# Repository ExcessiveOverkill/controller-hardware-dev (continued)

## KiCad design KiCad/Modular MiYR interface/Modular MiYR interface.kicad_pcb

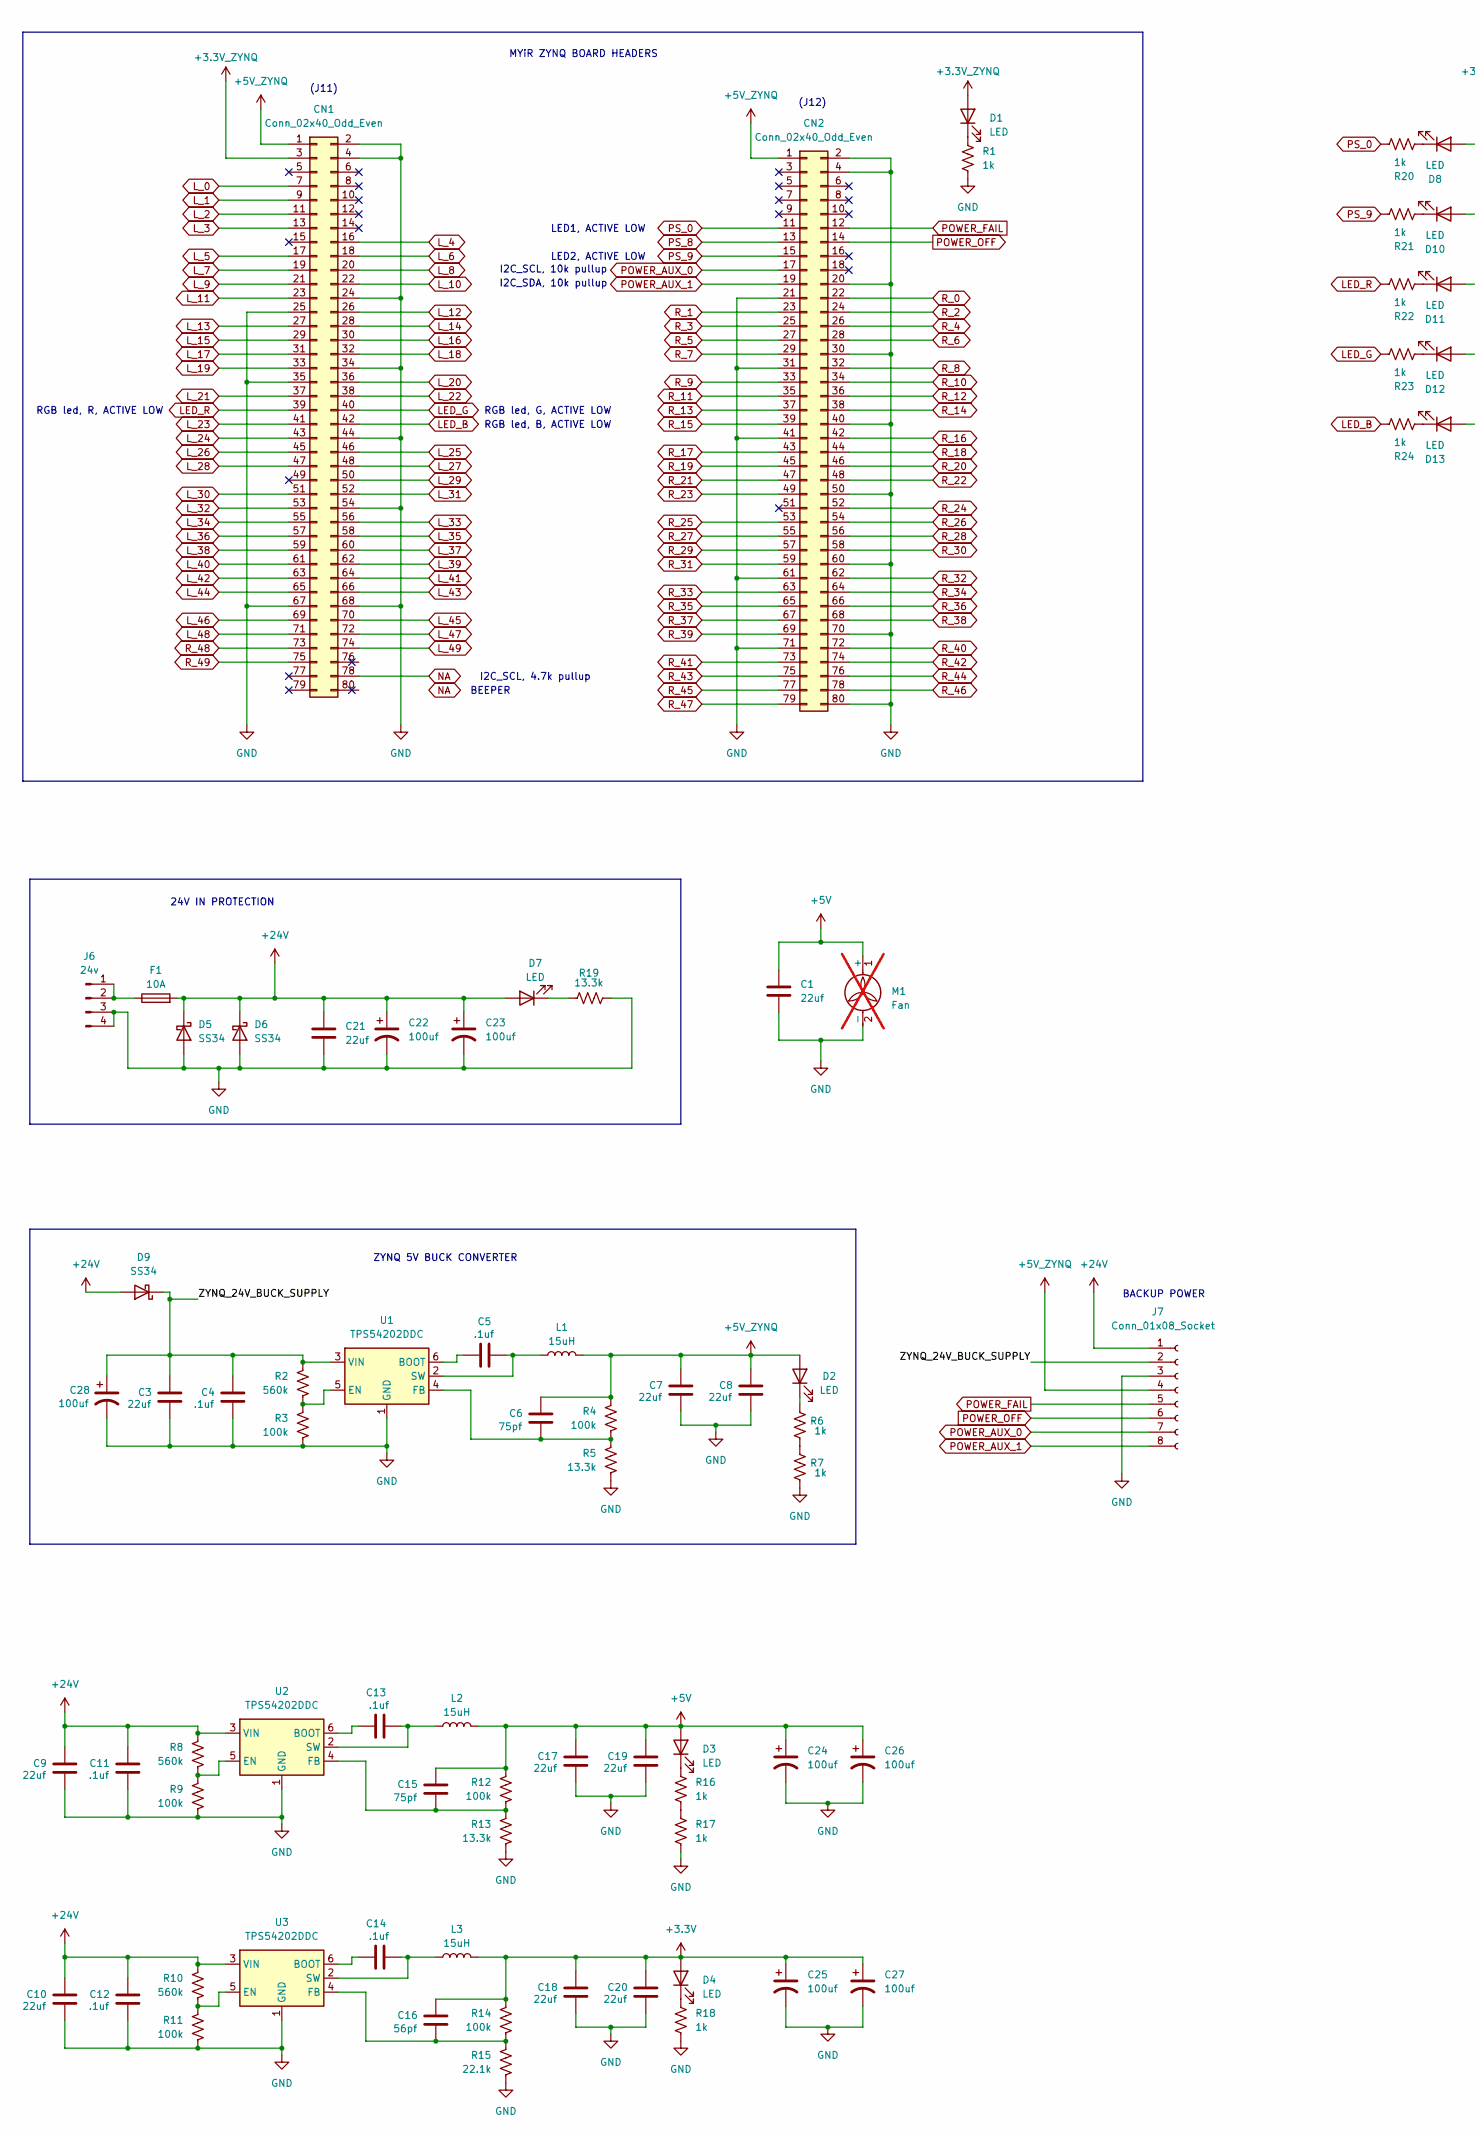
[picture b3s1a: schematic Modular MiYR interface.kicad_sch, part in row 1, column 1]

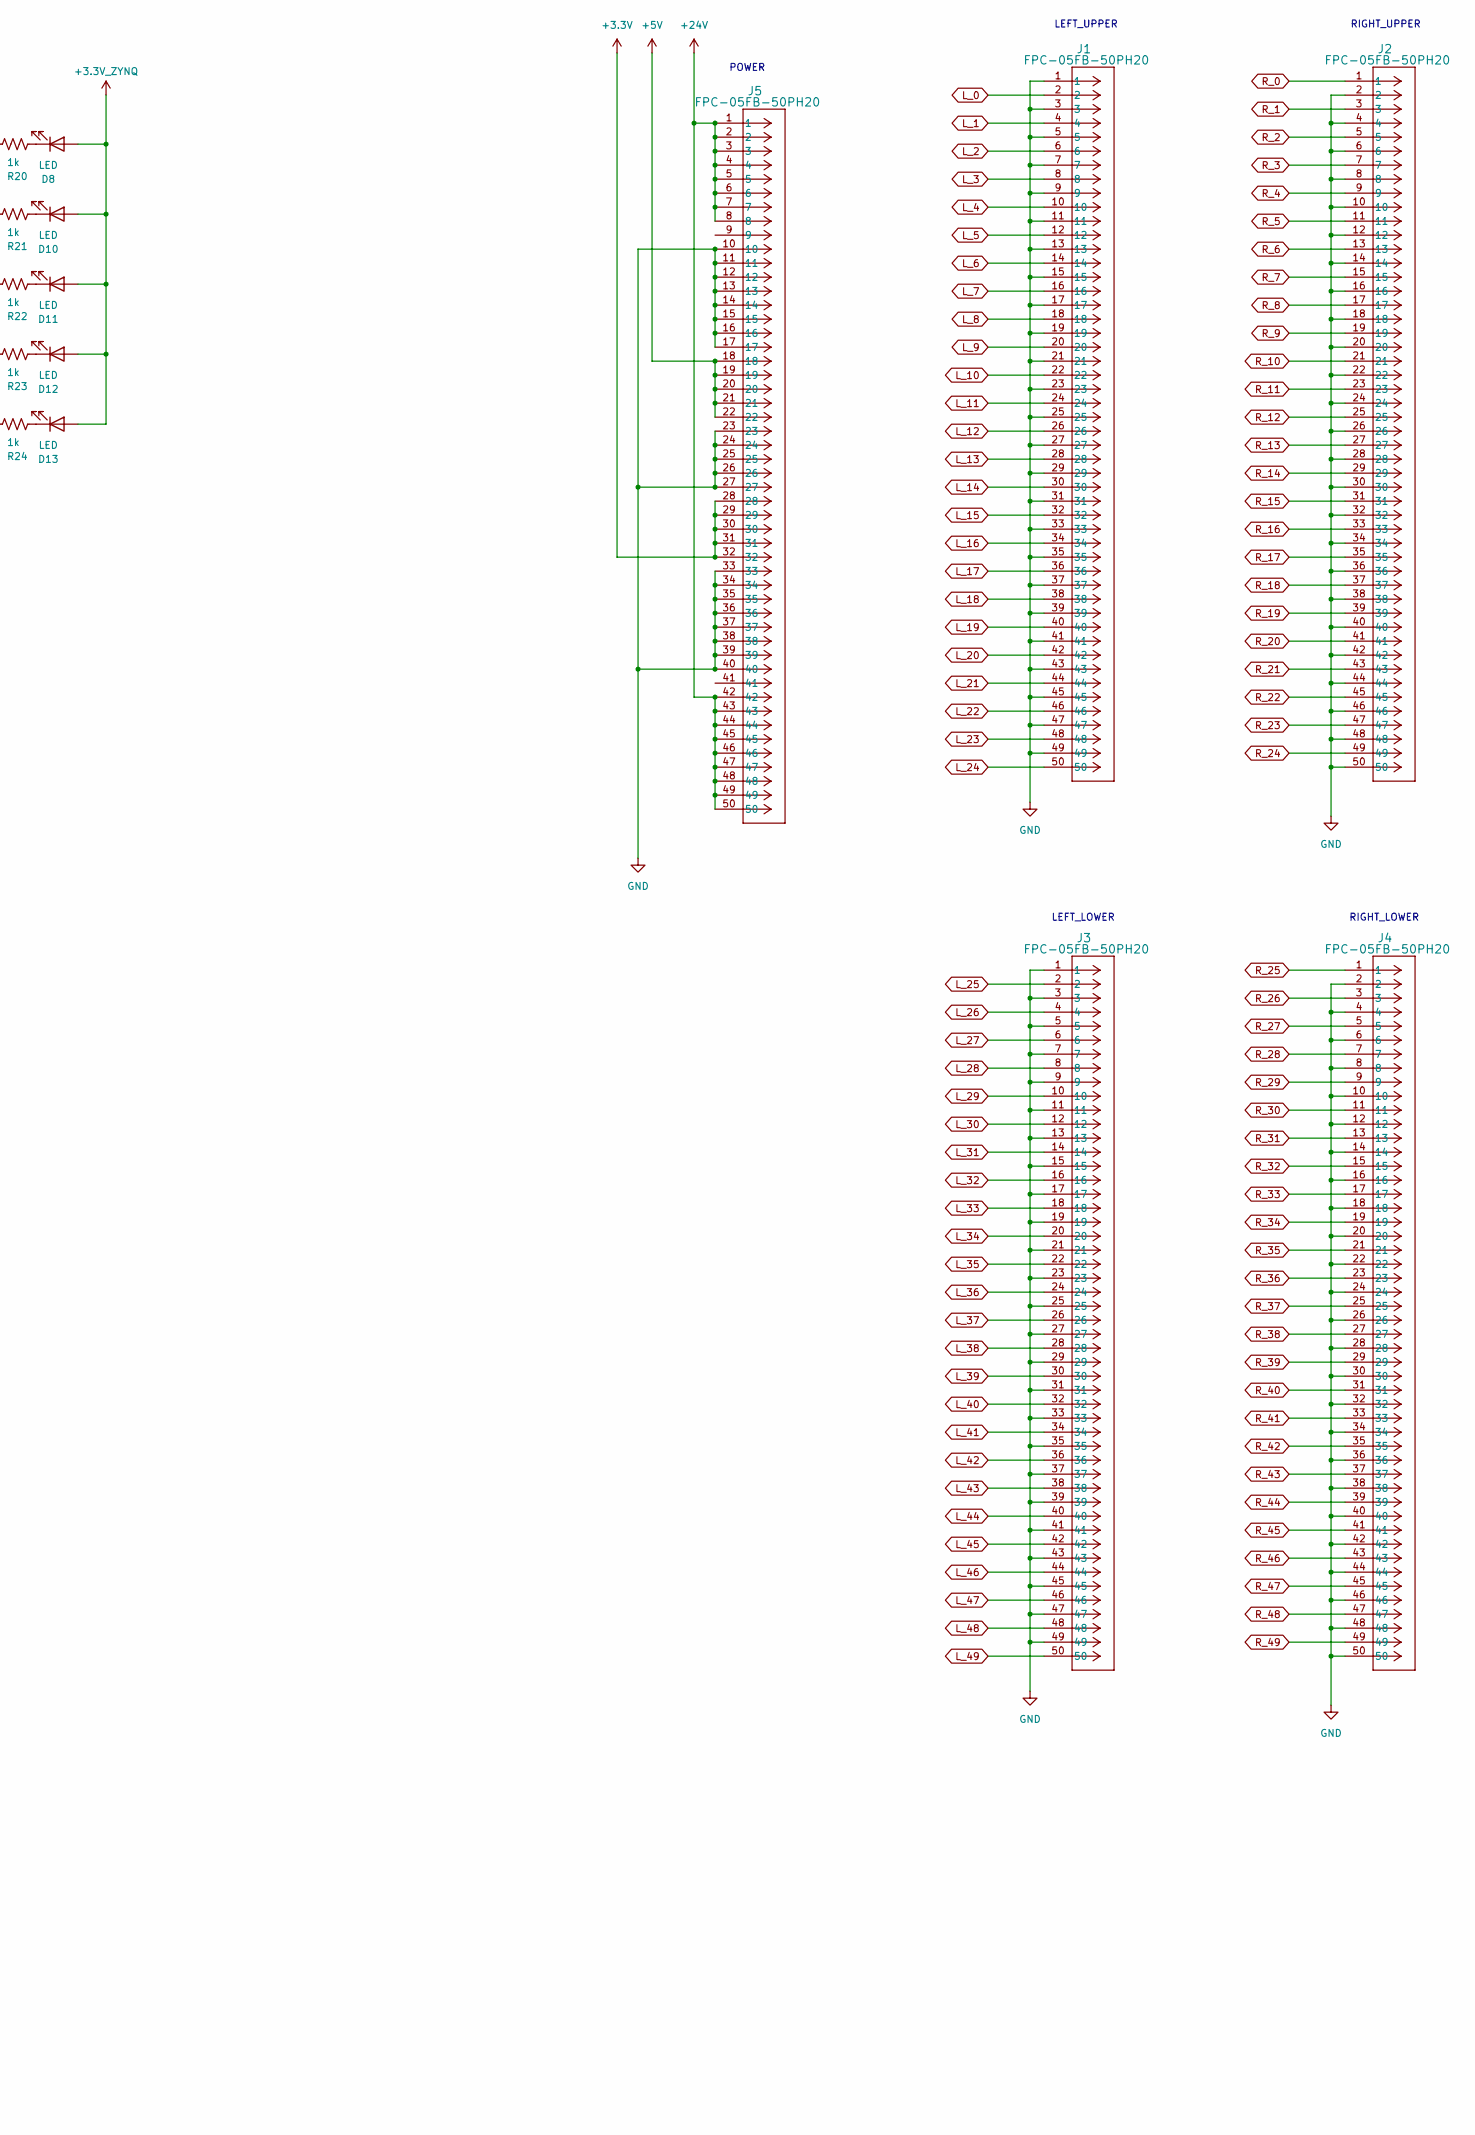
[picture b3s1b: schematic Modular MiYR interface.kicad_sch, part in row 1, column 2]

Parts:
C1, C3, C7, C8, C9, C10, C17, C18, C19, C20, C21: 22uf; C_1206_3216Metric; Part Number CL31A226KAHNNNE; LCSC# C12891
C4, C5, C11, C12, C13, C14: .1uf; C_0402_1005Metric; Part Number CC0402KRX5R9BB104; LCSC# C105882
C6, C15: 75pf; C_0402_1005Metric; Part Number CC0402JRNPO9BN750; LCSC# C107010
C16: 56pf; C_0402_1005Metric; Part Number CC0402JRNPO9BN560; LCSC# C107007
C22, C23, C24, C25, C26, C27, C28: 100uf; CP_Elec_6.3x7.7; Part Number RVT1V101M0607; LCSC# C72478
CN1, CN2: Conn_02x40_Odd_Even; PinHeader_2x40_P1.27mm_Vertical_SMD_FLIPPED; Part Number HDGC127-PS2-40; LCSC# C45359092
D1, D2, D3, D4, D7, D8, D10, D11, D12, D13: LED; LED_0603_1608Metric; Part Number XL-1608UBC-04; LCSC# C965807
D5, D6, D9: SS34; D_SMA; Part Number SS34; LCSC# C8678
F1: 10A; Fuse_1206_3216Metric; Part Number JFC1206-2100FS; LCSC# C136354
J1, J2, J3, J4, J5: FPC-05FB-50PH20; CONN50_FPC-05FB-50PH20_XNP
J6: 24v; 2x02_P3.5_KF2EDGSR
J7: Conn_01x08_Socket; PinHeader_1x08_P2.54mm_Vertical
L1, L2, L3: 15uH; CY54_INDUCTOR; Part Number CY54-15UH; LCSC# C2929432
M1: Fan; PinHeader_1x02_P2.54mm_Vertical; not fitted
R1, R6, R7, R16, R17, R18, R20, R21, R22, R23, R24: 1k; R_0402_1005Metric; Part Number RC0402FR-071KL; LCSC# C106235
R2, R8, R10: 560k; R_0402_1005Metric; Part Number RC0402FR-07560KL; LCSC# C137958
R3, R4, R9, R11, R12, R14: 100k; R_0402_1005Metric; Part Number RC0402FR-07100KL; LCSC# C60491
R5, R13, R19: 13.3k; R_0402_1005Metric; Part Number RC0402FR-0713K3L; LCSC# C274352
R15: 22.1k; R_0402_1005Metric; Part Number RC0402FR-0722K1L; LCSC# C163478
U1, U2, U3: TPS54202DDC; SOT-23-6; Part Number TPS54202DDCR; LCSC# C191884

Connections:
+3.3V: C16.2, C18.2, C20.2, C25.1, C27.1, D4.2 (A), J5.28, J5.29, J5.30, J5.31, J5.32, L3.2, R14.2
+3.3V_ZYNQ: CN1.3, D1.2 (A), D8.2 (A), D10.2 (A), D11.2 (A), D12.2 (A), D13.2 (A)
+5V: C1.1, C15.2, C17.2, C19.2, C24.1, C26.1, D3.2 (A), J5.18, J5.19, J5.20, J5.21, J5.22, L2.2, M1.1 (+), R12.2
+5V_ZYNQ: C6.2, C7.2, C8.2, CN1.1, CN2.1, D2.2 (A), J7.4, L1.2, R4.2
+24V: C9.2, C10.2, C11.2, C12.2, C21.1, C22.1, C23.1, D5.1 (K), D6.1 (K), D7.2 (A), D9.2 (A), F1.2, J5.1, J5.2, J5.3, J5.4, J5.5, J5.6, J5.7, J5.8, J5.42, J5.43, J5.44, J5.45, J5.46, J5.47, J5.48, J5.49, J5.50, J7.1, R8.2, R10.2, U2.3 (VIN), U3.3 (VIN)
/ZYNQ_24V_BUCK_SUPPLY: C3.2, C4.2, C28.1, D9.1 (K), J7.2, R2.2, U1.3 (VIN)
GND: C1.2, C3.1, C4.1, C7.1, C8.1, C9.1, C10.1, C11.1, C12.1, C17.1, C18.1, C19.1, C20.1, C21.2, C22.2, C23.2, C24.2, C25.2, C26.2, C27.2, C28.2, CN1.2, CN1.4, CN1.24, CN1.25, CN1.34, CN1.35, CN1.44, CN1.54, CN1.67, CN1.68, CN2.2, CN2.4, CN2.20, CN2.21, CN2.30, CN2.31, CN2.40, CN2.41, CN2.50, CN2.60, CN2.61, CN2.70, CN2.71, CN2.80, D5.2 (A), D6.2 (A), J1.1, J1.3, J1.5, J1.7, J1.9, J1.11, J1.13, J1.15, J1.17, J1.19, J1.21, J1.23, J1.25, J1.27, J1.29, J1.31, J1.33, J1.35, J1.37, J1.39, J1.41, J1.43, J1.45, J1.47, J1.49, J2.2, J2.4, J2.6, J2.8, J2.10, J2.12, J2.14, J2.16, J2.18, J2.20, J2.22, J2.24, J2.26, J2.28, J2.30, J2.32, J2.34, J2.36, J2.38, J2.40, J2.42, J2.44, J2.46, J2.48, J2.50, J3.1, J3.3, J3.5, J3.7, J3.9, J3.11, J3.13, J3.15, J3.17, J3.19, J3.21, J3.23, J3.25, J3.27, J3.29, J3.31, J3.33, J3.35, J3.37, J3.39, J3.41, J3.43, J3.45, J3.47, J3.49, J4.2, J4.4, J4.6, J4.8, J4.10, J4.12, J4.14, J4.16, J4.18, J4.20, J4.22, J4.24, J4.26, J4.28, J4.30, J4.32, J4.34, J4.36, J4.38, J4.40, J4.42, J4.44, J4.46, J4.48, J4.50, J5.10, J5.11, J5.12, J5.13, J5.14, J5.15, J5.16, J5.17, J5.23, J5.24, J5.25, J5.26, J5.27, J5.33, J5.34, J5.35, J5.36, J5.37, J5.38, J5.39, J5.40, J6.3, J6.4, J7.3, M1.2 (-), R1.1, R3.1, R5.1, R7.1, R9.1, R11.1, R13.1, R15.1, R17.1, R18.1, R19.1, U1.1 (GND), U2.1 (GND), U3.1 (GND)
LED_B: CN1.42, R24.1
LED_G: CN1.40, R23.1
LED_R: CN1.39, R22.1
L_0: CN1.7, J1.2
L_1: CN1.9, J1.4
L_2: CN1.11, J1.6
L_3: CN1.13, J1.8
L_4: CN1.16, J1.10
L_5: CN1.17, J1.12
L_6: CN1.18, J1.14
L_7: CN1.19, J1.16
L_8: CN1.20, J1.18
L_9: CN1.21, J1.20
L_10: CN1.22, J1.22
L_11: CN1.23, J1.24
L_12: CN1.26, J1.26
L_13: CN1.27, J1.28
L_14: CN1.28, J1.30
L_15: CN1.29, J1.32
L_16: CN1.30, J1.34
L_17: CN1.31, J1.36
L_18: CN1.32, J1.38
L_19: CN1.33, J1.40
L_20: CN1.36, J1.42
L_21: CN1.37, J1.44
L_22: CN1.38, J1.46
L_23: CN1.41, J1.48
L_24: CN1.43, J1.50
L_25: CN1.46, J3.2
L_26: CN1.45, J3.4
L_27: CN1.48, J3.6
L_28: CN1.47, J3.8
L_29: CN1.50, J3.10
L_30: CN1.51, J3.12
L_31: CN1.52, J3.14
L_32: CN1.53, J3.16
L_33: CN1.56, J3.18
L_34: CN1.55, J3.20
L_35: CN1.58, J3.22
L_36: CN1.57, J3.24
L_37: CN1.60, J3.26
L_38: CN1.59, J3.28
L_39: CN1.62, J3.30
L_40: CN1.61, J3.32
L_41: CN1.64, J3.34
L_42: CN1.63, J3.36
L_43: CN1.66, J3.38
L_44: CN1.65, J3.40
L_45: CN1.70, J3.42
L_46: CN1.69, J3.44
L_47: CN1.72, J3.46
L_48: CN1.71, J3.48
L_49: CN1.74, J3.50
NA: CN1.78
unnamed: D1.1 (K), R1.2
unnamed: D2.1 (K), R6.2
unnamed: D3.1 (K), R16.2
unnamed: D4.1 (K), R18.2
unnamed: D7.1 (K), R19.2
unnamed: D8.1 (K), R20.2
unnamed: D10.1 (K), R21.2
unnamed: D11.1 (K), R22.2
unnamed: D12.1 (K), R23.2
unnamed: D13.1 (K), R24.2
unnamed: F1.1, J6.1, J6.2
unnamed: R6.1, R7.2
unnamed: R16.1, R17.2
unnamed: C5.1, U1.6 (BOOT)
unnamed: R2.1, R3.2, U1.5 (EN)
unnamed: C6.1, R4.1, R5.2, U1.4 (FB)
unnamed: C5.2, L1.1, U1.2 (SW)
unnamed: C13.1, U2.6 (BOOT)
unnamed: R8.1, R9.2, U2.5 (EN)
unnamed: C15.1, R12.1, R13.2, U2.4 (FB)
unnamed: C13.2, L2.1, U2.2 (SW)
unnamed: C14.1, U3.6 (BOOT)
unnamed: R10.1, R11.2, U3.5 (EN)
unnamed: C16.1, R14.1, R15.2, U3.4 (FB)
unnamed: C14.2, L3.1, U3.2 (SW)
POWER_AUX_0: CN2.17, J7.7
POWER_AUX_1: CN2.19, J7.8
POWER_FAIL: CN2.12, J7.5
POWER_OFF: CN2.14, J7.6
PS_0: CN2.11, R20.1
PS_8: CN2.13
PS_9: CN2.15, R21.1
R_0: CN2.22, J2.1
R_1: CN2.23, J2.3
R_2: CN2.24, J2.5
R_3: CN2.25, J2.7
R_4: CN2.26, J2.9
R_5: CN2.27, J2.11
R_6: CN2.28, J2.13
R_7: CN2.29, J2.15
R_8: CN2.32, J2.17
R_9: CN2.33, J2.19
R_10: CN2.34, J2.21
R_11: CN2.35, J2.23
R_12: CN2.36, J2.25
R_13: CN2.37, J2.27
R_14: CN2.38, J2.29
R_15: CN2.39, J2.31
R_16: CN2.42, J2.33
R_17: CN2.43, J2.35
R_18: CN2.44, J2.37
R_19: CN2.45, J2.39
R_20: CN2.46, J2.41
R_21: CN2.47, J2.43
R_22: CN2.48, J2.45
R_23: CN2.49, J2.47
R_24: CN2.52, J2.49
R_25: CN2.53, J4.1
R_26: CN2.54, J4.3
R_27: CN2.55, J4.5
R_28: CN2.56, J4.7
R_29: CN2.57, J4.9
R_30: CN2.58, J4.11
R_31: CN2.59, J4.13
R_32: CN2.62, J4.15
R_33: CN2.63, J4.17
R_34: CN2.64, J4.19
R_35: CN2.65, J4.21
R_36: CN2.66, J4.23
R_37: CN2.67, J4.25
R_38: CN2.68, J4.27
R_39: CN2.69, J4.29
R_40: CN2.72, J4.31
R_41: CN2.73, J4.33
R_42: CN2.74, J4.35
R_43: CN2.75, J4.37
R_44: CN2.76, J4.39
R_45: CN2.77, J4.41
R_46: CN2.78, J4.43
R_47: CN2.79, J4.45
R_48: CN1.73, J4.47
R_49: CN1.75, J4.49

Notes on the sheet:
RIGHT_LOWER
MYiR ZYNQ BOARD HEADERS
BEEPER
24V IN PROTECTION
RGB led, B, ACTIVE LOW
POWER
ZYNQ 5V BUCK CONVERTER
RIGHT_UPPER
I2C_SCL, 10k pullup
RGB led, G, ACTIVE LOW
LED1, ACTIVE LOW
I2C_SDA, 10k pullup
LEFT_LOWER
(J11)
LED2, ACTIVE LOW
LEFT_UPPER
BACKUP POWER
I2C_SCL, 4.7k pullup
(J12)
RGB led, R, ACTIVE LOW

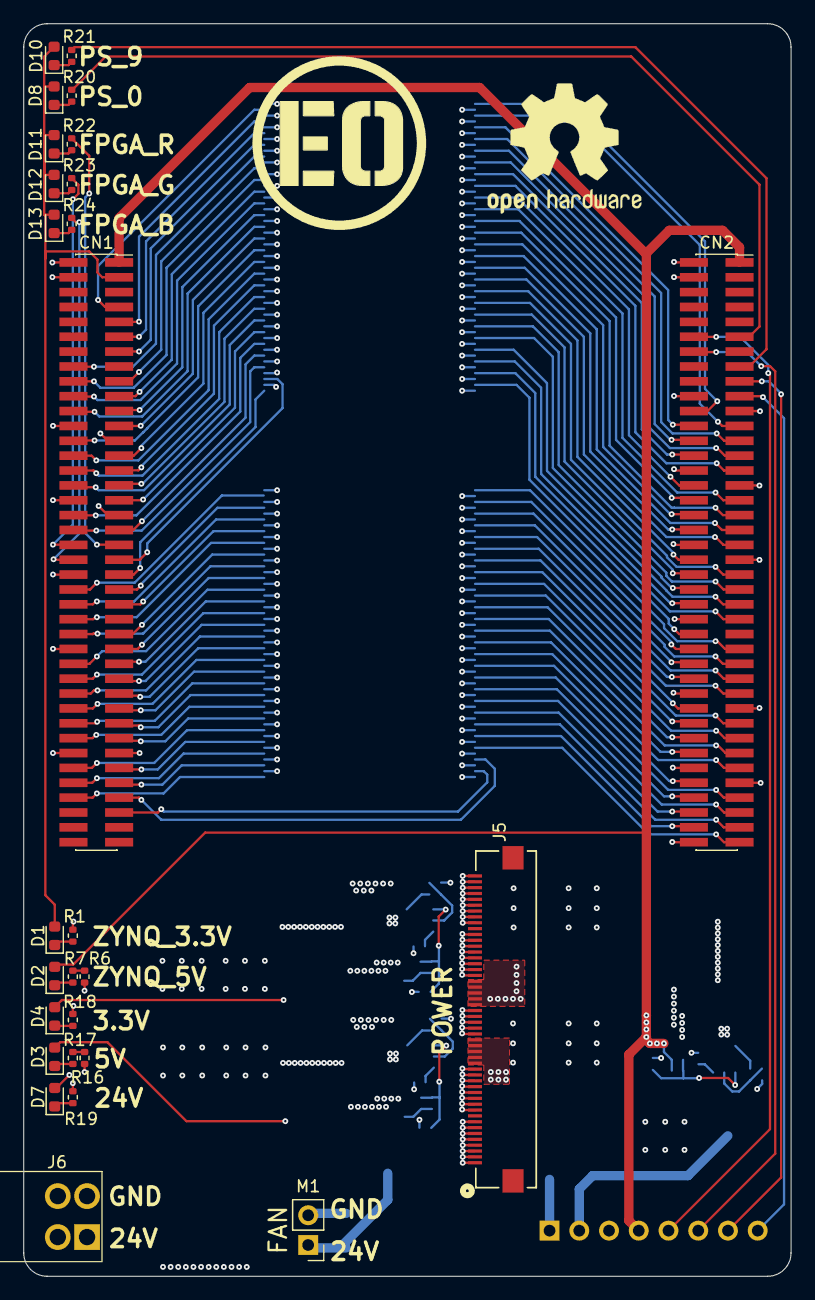
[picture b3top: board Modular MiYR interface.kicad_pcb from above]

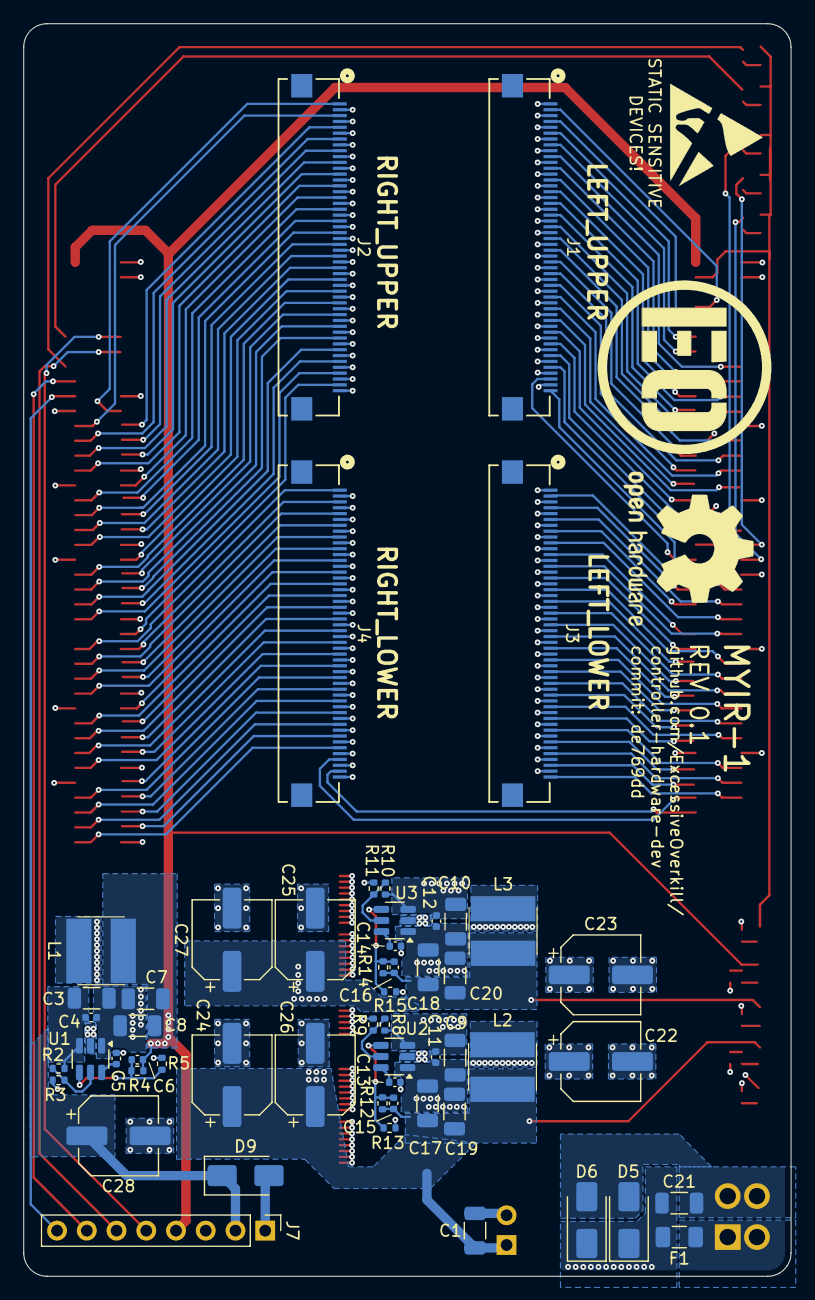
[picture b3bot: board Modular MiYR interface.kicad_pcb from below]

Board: 4 copper layers, 65.5 x 107.0 mm, 81 parts (54 on the bottom side), 141 nets.

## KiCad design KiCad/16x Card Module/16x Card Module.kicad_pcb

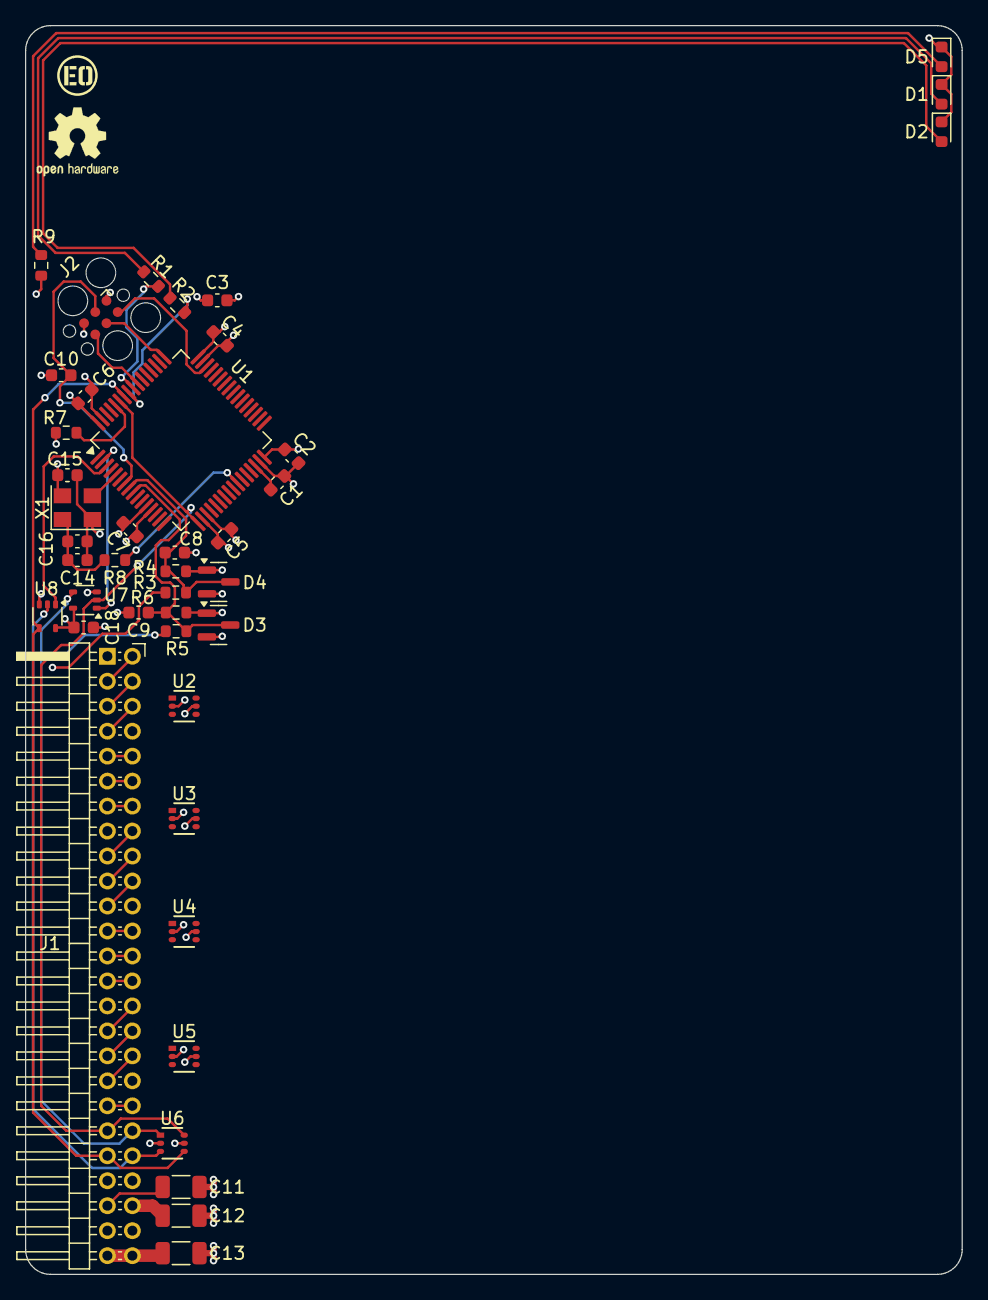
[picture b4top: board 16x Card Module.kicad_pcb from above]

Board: 4 copper layers, 75.0 x 100.0 mm, 42 parts (0 on the bottom side), 42 nets.

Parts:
C1, C3: 4.7uf; C_0603_1608Metric
C2, C4, C5, C6, C7, C8, C9, C10, C15, C16, C18: .1uf; C_0603_1608Metric
C11, C12, C13: 22uf; C_1206_3216Metric
C14: 2.2uf; C_0603_1608Metric
D1, D2, D5: LED; LED_0603_1608Metric
D3, D4: BAT54SLT1G; SOT-23
J1: Conn_02x25_Odd_Even; 16x_modular_card
J2: Conn_ARM_SWD_TagConnect_TC2030; Tag-Connect_TC2030-IDC-FP_2x03_P1.27mm_Vertical
R1, R2, R6, R8, R9: 1k; R_0603_1608Metric
R3, R4, R5, R7: 10k; R_0603_1608Metric
U1: STM32F411RETx; LQFP-64_10x10mm_P0.5mm
U2, U3, U4, U5, U6: D1213A-04S-7; SOT-363_DIO
U7, U8: 74LVC1G126; SOT-353_SC-70-5
X1: 16Mhz; Oscillator_SMD_SeikoEpson_SG8002CE-4Pin_3.2x2.5mm

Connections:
+3.3V: C2.1, C3.1, C4.1, C5.1, C6.1, C7.1, C12.2, C15.2, C18.2, D3.2 (K), D4.2 (K), J1.46, J2.1 (VCC), R9.1, U1.13 (VDDA), U1.19 (VDD), U1.32 (VDD), U1.48 (VDD), U1.64 (VDD), U2.5 (VCC), U3.5 (VCC), U4.5 (VCC), U5.5 (VCC), U6.5 (VCC), U7.5 (VCC), U8.5 (VCC), X1.4 (Vcc)
+5V: C11.2, J1.45, R3.1
+24V: C13.2, J1.49, J1.50, R5.1
/FPGA Connector/IN_0: J1.2, J1.3
/FPGA Connector/IN_1: J1.4, J1.5
/FPGA Connector/IN_2: J1.6, J1.7
/FPGA Connector/IN_3: J1.9, J1.10
/FPGA Connector/IN_4: J1.11, J1.12
/FPGA Connector/IN_5: J1.13, J1.14
/FPGA Connector/IN_6: J1.16, J1.17
/FPGA Connector/IN_7: J1.18, J1.19
/FPGA Connector/IN_8: J1.20, J1.21
/FPGA Connector/IN_9: J1.23, J1.24
/FPGA Connector/IN_10: J1.25, J1.26
/FPGA Connector/IN_11: J1.27, J1.28
/FPGA Connector/IN_12: J1.30, J1.31
/FPGA Connector/IN_13: J1.32, J1.33
/FPGA Connector/IN_14: J1.34, J1.35
/FPGA Connector/IN_15: J1.37, J1.38
/FPGA Connector/MODULE_RX: J1.42, U6.3 (CH2), U8.2
/FPGA Connector/MODULE_TX: J1.40, U6.1 (CH1), U7.4
/MCU/5V_SENSE: C8.1, D4.3 (common), R3.2, R4.1, U1.8 (PC0)
/MCU/24V_SENSE: C9.1, D3.3 (common), R5.2, R6.1, U1.9 (PC1)
/MCU/BOOT_SEL: R7.2, U1.60 (BOOT0)
/MCU/LED_0: R1.1, U1.56 (PB4)
/MCU/LED_1: R2.1, U1.57 (PB5)
/MCU/NRESET: C10.2, J2.3 (~RESET), U1.7 (NRST)
/MCU/OSC: U1.5 (PH0), X1.3 (OUT)
/MCU/RX: J1.39, U1.17 (PA3), U1.59 (PB7), U6.6 (CH4), U7.2
/MCU/RX_PASSTHROUGH_ENABLE: U1.3 (PC14), U8.1
/MCU/SWCLK: J2.4 (SWCLK), U1.49 (PA14)
/MCU/SWDIO: J2.2 (SWDIO), U1.46 (PA13)
/MCU/SWO: J2.6 (SWO), U1.55 (PB3)
/MCU/TX: J1.41, U1.58 (PB6), U6.4 (CH3), U8.4
/MCU/TX_PASSTHROUGH_ENABLE: U1.2 (PC13), U7.1
/MCU/VCXO_TRIM: R8.1, U1.26 (PB0)
GND: C1.2, C2.2, C3.2, C4.2, C5.2, C6.2, C7.2, C8.2, C9.2, C10.1, C11.1, C12.1, C13.1, C14.1, C15.1, C16.1, C18.1, D1.1 (K), D2.1 (K), D3.1 (A), D4.1 (A), D5.1 (K), J1.1, J1.8, J1.15, J1.22, J1.29, J1.36, J1.43, J1.44, J1.47, J1.48, J2.5 (GND), R4.2, R6.2, R7.1, U1.12 (VSSA), U1.18 (VSS), U1.31 (VSS), U1.47 (VSS), U1.63 (VSS), U2.2 (GND), U3.2 (GND), U4.2 (GND), U5.2 (GND), U6.2 (GND), U7.3 (GND), U8.3 (GND), X1.2 (GND)
unnamed: D1.2 (A), R1.2
unnamed: D2.2 (A), R2.2
unnamed: D5.2 (A), R9.2
unnamed: C1.1, U1.30 (VCAP1)
unnamed: C14.2, C16.2, R8.2, X1.1 (OE)

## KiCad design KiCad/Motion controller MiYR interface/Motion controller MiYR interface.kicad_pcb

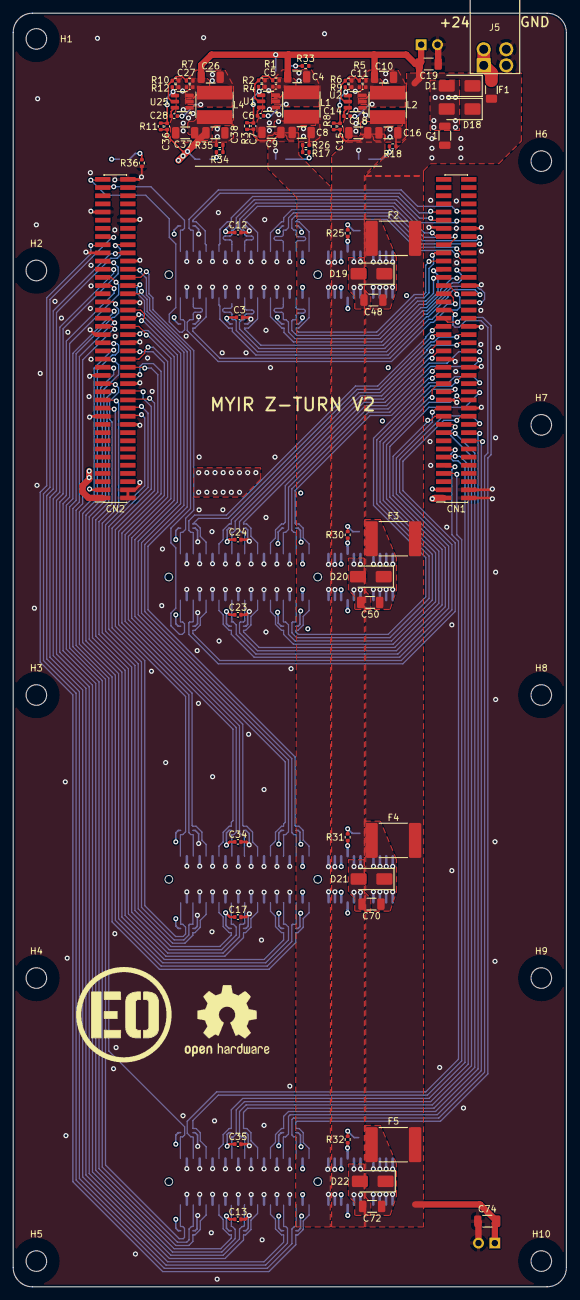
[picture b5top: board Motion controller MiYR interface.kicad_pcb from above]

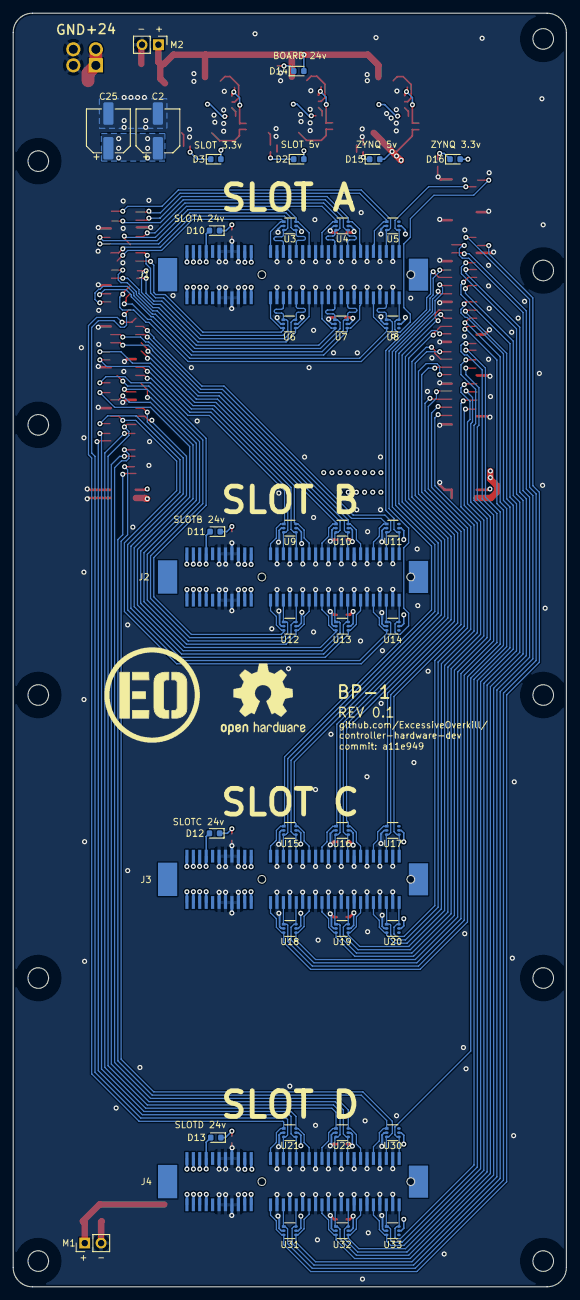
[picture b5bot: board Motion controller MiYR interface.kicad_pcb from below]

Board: 4 copper layers, 86.0 x 198.0 mm, 127 parts (41 on the bottom side), 122 nets.

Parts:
C1, C19, C48, C50, C70, C72, C74: 10uf; C_1206_3216Metric
C2, C25: 100uf; CP_Elec_6.3x7.7
C3, C5, C6, C11, C12, C13, C14, C17, C23, C24, C27, C28, C34, C35: .1uf; C_0402_1005Metric
C4, C8, C9, C10, C16, C18, C26, C37, C38: 22uf; C_1206_3216Metric
C7, C36: 75pf; C_0402_1005Metric
C15: 56pf; C_0402_1005Metric
CN1, CN2: Conn_02x40_Odd_Even; PinHeader_2x40_P1.27mm_Vertical_SMD_FLIPPED
D1, D18, D19, D20, D21, D22: SS34; D_SMA
D2, D3, D10, D11, D12, D13, D14, D15, D16: LED; LED_0603_1608Metric
F1: 10A; Fuse_1206_3216Metric
F2, F3, F4, F5: 3A; Fuse_2920_7451Metric
H1, H2, H3, H4, H5, H6, H7, H8, H9, H10: MountingHole; MountingHole_3.2mm_M3
J1, J2, J3, J4: 10061913-111PLF; PCI_64_SMD_CONNECTOR
J5: 24v; 2x02_P3.5_KF2EDGSR
L1, L2, L4: 15uH; CY54_INDUCTOR
M1, M2: Fan; PinHeader_1x02_P2.54mm_Vertical
R1, R5, R7: 500k; R_0402_1005Metric
R2, R3, R6, R8, R10, R11: 100k; R_0402_1005Metric
R4, R12, R25, R30, R31, R32, R33: 13.3k; R_0402_1005Metric
R9: 22.1k; R_0402_1005Metric
R17, R18, R26, R34, R35, R36: 1k; R_0402_1005Metric
U1, U2, U25: TPS54202DDC; SOT-23-6
U3, U4, U5, U6, U7, U8, U9, U10, U11, U12, U13, U14, U15, U16, U17, U18, U19, U20, U21, U22, U30, U31, U32, U33: D1213A-04S-7; SOT-363_DIO

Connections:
+3.3V: C3.1, C12.1, C13.1, C17.1, C23.1, C24.1, C34.1, C35.1, CN1.3, CN2.3, D16.2 (A), U3.5 (VCC), U4.5 (VCC), U5.5 (VCC), U6.5 (VCC), U7.5 (VCC), U8.5 (VCC), U9.5 (VCC), U10.5 (VCC), U11.5 (VCC), U12.5 (VCC), U13.5 (VCC), U14.5 (VCC), U15.5 (VCC), U16.5 (VCC), U17.5 (VCC), U18.5 (VCC), U19.5 (VCC), U20.5 (VCC), U21.5 (VCC), U22.5 (VCC), U30.5 (VCC), U31.5 (VCC), U32.5 (VCC), U33.5 (VCC)
+3.3VA: C15.2, C16.2, C18.2, D3.2 (A), J1.P$A10 (A10), J1.P$B10 (B10), J2.P$A10 (A10), J2.P$B10 (B10), J3.P$A10 (A10), J3.P$B10 (B10), J4.P$A10 (A10), J4.P$B10 (B10), L2.2, R8.2
+5V: C36.2, C37.2, C38.2, CN1.1, CN2.1, D15.2 (A), L4.2, R11.2
+5VA: C7.2, C8.2, C9.2, D2.2 (A), J1.P$A11 (A11), J1.P$B11 (B11), J2.P$A11 (A11), J2.P$B11 (B11), J3.P$A11 (A11), J3.P$B11 (B11), J4.P$A11 (A11), J4.P$B11 (B11), L1.2, R3.2
+24V: C1.1, C2.1, C4.2, C5.2, C10.2, C11.2, C19.1, C25.1, C26.2, C27.2, C74.1, D1.1 (K), D14.2 (A), D18.1 (K), F1.2, F2.1, F3.1, F4.1, F5.1, M1.1 (+), M2.1 (+), R1.2, R5.2, R7.2, U1.3 (VIN), U2.3 (VIN), U25.3 (VIN)
GND: C1.2, C2.2, C3.2, C4.1, C5.1, C8.1, C9.1, C10.1, C11.1, C12.2, C13.2, C16.1, C17.2, C18.1, C19.2, C23.2, C24.2, C25.2, C26.1, C27.1, C34.2, C35.2, C37.1, C38.1, C48.2, C50.2, C70.2, C72.2, C74.2, CN1.2, CN1.4, CN1.24, CN1.25, CN1.34, CN1.35, CN1.44, CN1.54, CN1.67, CN1.68, CN2.2, CN2.4, CN2.20, CN2.21, CN2.30, CN2.31, CN2.40, CN2.41, CN2.50, CN2.60, CN2.61, CN2.70, CN2.71, CN2.80, D1.2 (A), D18.2 (A), D19.2 (A), D20.2 (A), D21.2 (A), D22.2 (A), J1.P$A6 (A6), J1.P$A7 (A7), J1.P$A8 (A8), J1.P$A9 (A9), J1.P$A13 (A13), J1.P$A15 (A15), J1.P$A17 (A17), J1.P$A19 (A19), J1.P$A21 (A21), J1.P$A23 (A23), J1.P$A25 (A25), J1.P$A27 (A27), J1.P$A29 (A29), J1.P$A31 (A31), J1.P$B6 (B6), J1.P$B7 (B7), J1.P$B8 (B8), J1.P$B9 (B9), J1.P$B13 (B13), J1.P$B15 (B15), J1.P$B17 (B17), J1.P$B19 (B19), J1.P$B21 (B21), J1.P$B23 (B23), J1.P$B25 (B25), J1.P$B27 (B27), J1.P$B29 (B29), J1.P$B31 (B31), J2.P$A6 (A6), J2.P$A7 (A7), J2.P$A8 (A8), J2.P$A9 (A9), J2.P$A13 (A13), J2.P$A15 (A15), J2.P$A17 (A17), J2.P$A19 (A19), J2.P$A21 (A21), J2.P$A23 (A23), J2.P$A25 (A25), J2.P$A27 (A27), J2.P$A29 (A29), J2.P$A31 (A31), J2.P$B6 (B6), J2.P$B7 (B7), J2.P$B8 (B8), J2.P$B9 (B9), J2.P$B13 (B13), J2.P$B15 (B15), J2.P$B17 (B17), J2.P$B19 (B19), J2.P$B21 (B21), J2.P$B23 (B23), J2.P$B25 (B25), J2.P$B27 (B27), J2.P$B29 (B29), J2.P$B31 (B31), J3.P$A6 (A6), J3.P$A7 (A7), J3.P$A8 (A8), J3.P$A9 (A9), J3.P$A13 (A13), J3.P$A15 (A15), J3.P$A17 (A17), J3.P$A19 (A19), J3.P$A21 (A21), J3.P$A23 (A23), J3.P$A25 (A25), J3.P$A27 (A27), J3.P$A29 (A29), J3.P$A31 (A31), J3.P$B6 (B6), J3.P$B7 (B7), J3.P$B8 (B8), J3.P$B9 (B9), J3.P$B13 (B13), J3.P$B15 (B15), J3.P$B17 (B17), J3.P$B19 (B19), J3.P$B21 (B21), J3.P$B23 (B23), J3.P$B25 (B25), J3.P$B27 (B27), J3.P$B29 (B29), J3.P$B31 (B31), J4.P$A6 (A6), J4.P$A7 (A7), J4.P$A8 (A8), J4.P$A9 (A9), J4.P$A13 (A13), J4.P$A15 (A15), J4.P$A17 (A17), J4.P$A19 (A19), J4.P$A21 (A21), J4.P$A23 (A23), J4.P$A25 (A25), J4.P$A27 (A27), J4.P$A29 (A29), J4.P$A31 (A31), J4.P$B6 (B6), J4.P$B7 (B7), J4.P$B8 (B8), J4.P$B9 (B9), J4.P$B13 (B13), J4.P$B15 (B15), J4.P$B17 (B17), J4.P$B19 (B19), J4.P$B21 (B21), J4.P$B23 (B23), J4.P$B25 (B25), J4.P$B27 (B27), J4.P$B29 (B29), J4.P$B31 (B31), J5.3, J5.4, M1.2 (-), M2.2 (-), R2.1, R4.1, R6.1, R9.1, R10.1, R12.1, R18.1, R25.1, R26.1, R30.1, R31.1, R32.1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
unnamed: D2.1 (K), R17.2
unnamed: D3.1 (K), R18.2
unnamed: D10.1 (K), R25.2
unnamed: D11.1 (K), R30.2
unnamed: D12.1 (K), R31.2
unnamed: D13.1 (K), R32.2
unnamed: D14.1 (K), R33.2
unnamed: D15.1 (K), R34.2
unnamed: D16.1 (K), R36.2
unnamed: F1.1, J5.1, J5.2
unnamed: R17.1, R26.2
unnamed: R34.1, R35.2
unnamed: C6.1, U1.6 (BOOT)
unnamed: R1.1, R2.2, U1.5 (EN)
unnamed: C7.1, R3.1, R4.2, U1.4 (FB)
unnamed: C6.2, L1.1, U1.2 (SW)
unnamed: C14.1, U2.6 (BOOT)
unnamed: R5.1, R6.2, U2.5 (EN)
unnamed: C15.1, R8.1, R9.2, U2.4 (FB)
unnamed: C14.2, L2.1, U2.2 (SW)
unnamed: C28.1, U25.6 (BOOT)
unnamed: R7.1, R10.2, U25.5 (EN)
unnamed: C36.1, R11.1, R12.2, U25.4 (FB)
unnamed: C28.2, L4.1, U25.2 (SW)
SLOT A 24V: C48.1, D10.2 (A), D19.1 (K), F2.2, J1.P$A1 (A1), J1.P$A2 (A2), J1.P$A3 (A3), J1.P$A4 (A4), J1.P$B1 (B1), J1.P$B2 (B2), J1.P$B3 (B3), J1.P$B4 (B4)
SLOT B 24V: C50.1, D11.2 (A), D20.1 (K), F3.2, J2.P$A1 (A1), J2.P$A2 (A2), J2.P$A3 (A3), J2.P$A4 (A4), J2.P$B1 (B1), J2.P$B2 (B2), J2.P$B3 (B3), J2.P$B4 (B4)
SLOT C 24V: C70.1, D12.2 (A), D21.1 (K), F4.2, J3.P$A1 (A1), J3.P$A2 (A2), J3.P$A3 (A3), J3.P$A4 (A4), J3.P$B1 (B1), J3.P$B2 (B2), J3.P$B3 (B3), J3.P$B4 (B4)
SLOT D 24V: C72.1, D13.2 (A), D22.1 (K), F5.2, J4.P$A1 (A1), J4.P$A2 (A2), J4.P$A3 (A3), J4.P$A4 (A4), J4.P$B1 (B1), J4.P$B2 (B2), J4.P$B3 (B3), J4.P$B4 (B4)
SLOTA1N: CN1.62, J1.P$A14 (A14), U3.3 (CH2)
SLOTA1P: CN1.60, J1.P$A12 (A12), U3.1 (CH1)
SLOTA2N: CN1.66, J1.P$A18 (A18), U3.6 (CH4)
SLOTA2P: CN1.64, J1.P$A16 (A16), U3.4 (CH3)
SLOTA3N: CN1.65, J1.P$A22 (A22), U4.3 (CH2)
SLOTA3P: CN1.63, J1.P$A20 (A20), U4.1 (CH1)
SLOTA4N: CN1.69, J1.P$A26 (A26), U4.6 (CH4)
SLOTA4P: CN1.70, J1.P$A24 (A24), U4.4 (CH3)
SLOTA5N: CN1.72, J1.P$A30 (A30), U5.3 (CH2)
SLOTA5P: CN1.71, J1.P$A28 (A28), U5.1 (CH1)
SLOTA6N: CN1.61, J1.P$B14 (B14), U6.1 (CH1)
SLOTA6P: CN1.59, J1.P$B12 (B12), U6.3 (CH2)
SLOTA7N: CN1.57, J1.P$B18 (B18), U6.4 (CH3)
SLOTA7P: CN1.55, J1.P$B16 (B16), U6.6 (CH4)
SLOTA8N: CN1.58, J1.P$B22 (B22), U7.1 (CH1)
SLOTA8P: CN1.56, J1.P$B20 (B20), U7.3 (CH2)
SLOTA9N: CN1.52, J1.P$B26 (B26), U7.4 (CH3)
SLOTA9P: CN1.50, J1.P$B24 (B24), U7.6 (CH4)
SLOTA10N: CN1.53, J1.P$B30 (B30), U8.1 (CH1)
SLOTA10P: CN1.51, J1.P$B28 (B28), U8.3 (CH2)
SLOTA11N: CN2.79, J1.P$B32 (B32), U8.6 (CH4)
SLOTA11P: CN2.77, J1.P$A32 (A32), U5.4 (CH3)
SLOTB1N: CN1.33, J2.P$A14 (A14), U9.3 (CH2)
SLOTB1P: CN1.31, J2.P$A12 (A12), U9.1 (CH1)
SLOTB2N: CN1.38, J2.P$A18 (A18), U9.6 (CH4)
SLOTB2P: CN1.36, J2.P$A16 (A16), U9.4 (CH3)
SLOTB3N: CN1.39, J2.P$A22 (A22), U10.3 (CH2)
SLOTB3P: CN1.37, J2.P$A20 (A20), U10.1 (CH1)
SLOTB4N: CN1.42, J2.P$A26 (A26), U10.6 (CH4)
SLOTB4P: CN1.40, J2.P$A24 (A24), U10.4 (CH3)
SLOTB5N: CN1.43, J2.P$A30 (A30), U11.3 (CH2)
SLOTB5P: CN1.41, J2.P$A28 (A28), U11.1 (CH1)
SLOTB6N: CN1.32, J2.P$B14 (B14), U12.1 (CH1)
SLOTB6P: CN1.30, J2.P$B12 (B12), U12.3 (CH2)
SLOTB7N: CN1.29, J2.P$B18 (B18), U12.4 (CH3)
SLOTB7P: CN1.27, J2.P$B16 (B16), U12.6 (CH4)
SLOTB8N: CN1.28, J2.P$B22 (B22), U13.1 (CH1)
SLOTB8P: CN1.26, J2.P$B20 (B20), U13.3 (CH2)
SLOTB9N: CN1.23, J2.P$B26 (B26), U13.4 (CH3)
SLOTB9P: CN1.21, J2.P$B24 (B24), U13.6 (CH4)
SLOTB10N: CN1.22, J2.P$B30 (B30), U14.1 (CH1)
SLOTB10P: CN1.20, J2.P$B28 (B28), U14.3 (CH2)
SLOTB11N: CN2.58, J2.P$B32 (B32), U14.6 (CH4)
SLOTB11P: CN2.56, J2.P$A32 (A32), U11.4 (CH3)
SLOTC1N: CN2.54, J3.P$A14 (A14), U15.3 (CH2)
SLOTC1P: CN2.52, J3.P$A12 (A12), U15.1 (CH1)
SLOTC2N: CN2.48, J3.P$A18 (A18), U15.6 (CH4)
SLOTC2P: CN2.46, J3.P$A16 (A16), U15.4 (CH3)
SLOTC3N: CN2.44, J3.P$A22 (A22), U16.3 (CH2)
SLOTC3P: CN2.42, J3.P$A20 (A20), U16.1 (CH1)
SLOTC4N: CN2.38, J3.P$A26 (A26), U16.6 (CH4)
SLOTC4P: CN2.36, J3.P$A24 (A24), U16.4 (CH3)
SLOTC5N: CN2.34, J3.P$A30 (A30), U17.3 (CH2)
SLOTC5P: CN2.32, J3.P$A28 (A28), U17.1 (CH1)
SLOTC6N: CN2.39, J3.P$B14 (B14), U18.1 (CH1)
SLOTC6P: CN2.37, J3.P$B12 (B12), U18.3 (CH2)
SLOTC7N: CN2.35, J3.P$B18 (B18), U18.4 (CH3)
SLOTC7P: CN2.33, J3.P$B16 (B16), U18.6 (CH4)
SLOTC8N: CN2.29, J3.P$B22 (B22), U19.1 (CH1)
SLOTC8P: CN2.27, J3.P$B20 (B20), U19.3 (CH2)
SLOTC9N: CN2.25, J3.P$B26 (B26), U19.4 (CH3)
SLOTC9P: CN2.23, J3.P$B24 (B24), U19.6 (CH4)
SLOTC10N: CN2.24, J3.P$B30 (B30), U20.1 (CH1)
SLOTC10P: CN2.22, J3.P$B28 (B28), U20.3 (CH2)
SLOTC11N: CN2.28, J3.P$B32 (B32), U20.6 (CH4)
SLOTC11P: CN2.26, J3.P$A32 (A32), U17.4 (CH3)
SLOTD1N: CN1.47, J4.P$A14 (A14), U21.3 (CH2)
SLOTD1P: CN1.45, J4.P$A12 (A12), U21.1 (CH1)
SLOTD2N: CN1.18, J4.P$A18 (A18), U21.6 (CH4)
SLOTD2P: CN1.16, J4.P$A16 (A16), U21.4 (CH3)
SLOTD3N: CN1.19, J4.P$A22 (A22), U22.3 (CH2)
SLOTD3P: CN1.17, J4.P$A20 (A20), U22.1 (CH1)
SLOTD4N: CN1.13, J4.P$A26 (A26), U22.6 (CH4)
SLOTD4P: CN1.11, J4.P$A24 (A24), U22.4 (CH3)
SLOTD5N: CN1.9, J4.P$A30 (A30), U30.3 (CH2)
SLOTD5P: CN1.7, J4.P$A28 (A28), U30.1 (CH1)
SLOTD6N: CN2.65, J4.P$B14 (B14), U31.1 (CH1)
SLOTD6P: CN2.63, J4.P$B12 (B12), U31.3 (CH2)
SLOTD7N: CN2.64, J4.P$B18 (B18), U31.4 (CH3)
SLOTD7P: CN2.62, J4.P$B16 (B16), U31.6 (CH4)
SLOTD8N: CN2.59, J4.P$B22 (B22), U32.1 (CH1)
SLOTD8P: CN2.57, J4.P$B20 (B20), U32.3 (CH2)
SLOTD9N: CN2.55, J4.P$B26 (B26), U32.4 (CH3)
SLOTD9P: CN2.53, J4.P$B24 (B24), U32.6 (CH4)
SLOTD10N: CN2.49, J4.P$B30 (B30), U33.1 (CH1)
SLOTD10P: CN2.47, J4.P$B28 (B28), U33.3 (CH2)
SLOTD11N: CN2.45, J4.P$B32 (B32), U33.6 (CH4)
SLOTD11P: CN2.43, J4.P$A32 (A32), U30.4 (CH3)

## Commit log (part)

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2026-01-11 add modular boards
2026-01-15 update boards
2026-01-15 fix jumper
2026-05-09 work on serial module
